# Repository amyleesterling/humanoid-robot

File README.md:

# Project Button — build convergence

**Selected engineering candidate: HR30-TETHER-LIGHT4-P0.1. Not a build release.**

Button remains a complete 762 mm humanoid with 25 active axes, two functional hands, a face, audio/vision, conversational intelligence, and a local deterministic motion boundary. Whole-body walking remains the goal. An instrumented joint is development equipment, not a replacement deliverable. Tether-first testing does not silently remove the eventual onboard-power and untethered requirements.

## Start here

[Active whole-body visual guide](hr30/whole-body-p0.1/active-light4-p0.1/index.html) · [Complete engineering showcase](hr30/whole-body-p0.1/index.html) · [Critical-joint test package](hr30/build-release/critical-joint-test.md) · [Open release decisions](hr30/build-release/blockers.csv)

The machine-readable [baseline lock](hr30/build-release/baseline.lock.json) selects exact existing artifacts at commit `174691255409336a7e25ba1505217859c98c3f80`; it does not regenerate or copy the robot. This is the entry point for the build-release sprint. Older generated package pages retain historical values and must not override these explicit roles.

| Role | Selected source / boundary |
| --- | --- |
| Whole-body geometry | `lightweight-hip-successor-p0.1/HR-30_light4_whole_body_candidate.step` and matching GLB under `hr30/whole-body-p0.1/` |
| Dynamics model | `active-light4-p0.1/hr30_tether_light4_active.urdf` and `.xml` |
| Existing control evidence | `active-light4-p0.1/hr30_tether_light4_ideal_fixture.xml`; the base is supported by a six-degree-of-freedom trajectory weld, not free balance |
| Current planning mass | 9.879813509 kg; 0.120186491 kg below the 10 kg ceiling; no as-built mass or adequate reserve demonstrated |
| Hip pitch/roll | LIGHT4 4:1 on four axes; the old 1.5:1 pitch / 2:1 roll allocation rows are explicitly superseded |
| First test candidate | `R_ANKLE_PITCH`, XM430-W350-R with the LD-25 2.5:1 drive; decision experiment, not approved hardware |
| Other systems | Existing electrical, harness and software packages remain candidates; cross-system build-release reconciliation is open |

The 9.928 kg base ledger and the earlier control-successor result are not the selected LIGHT4 mass/control evidence. The older allocation CSV is reused for its unchanged ankle definition, not adopted wholesale as the active hip allocation. The checker records those four supersessions explicitly.

## Reproduce this sprint's checks

Python 3.10+; standard library only. No network, hardware connection, CAD toolchain, or simulator is invoked.

```sh
python tools/check_hr30_build_baseline.py
python -m unittest discover -s tests -p 'test_hr30_build_baseline.py' -v
# Optional: verify the nine referenced larger assets, if present locally.
python tools/check_hr30_build_baseline.py --full-assets
```

Default execution verifies the exact SHA-256 of three small source files, checks all 23 rotary demand rows and the reduced-leg allocation, reproduces the mass and joint-selection arithmetic, and totals the budget. The two grippers are not silently counted as rotary torque rows. `--full-assets` hashes additional files; even that does not validate geometry, structural capacity, or physics.

On 2026-09-25, the default audit ran against three connector-retrieved source snapshots whose bytes matched the existing source-manifest hashes. **31 synthetic software tests passed**, including stale hashes, missing/duplicate axes, NaN, invalid ratios, authority promotion, wrong adapters, and budget errors. See [the generated audit result](hr30/build-release/validation.json). No complete clone, large-asset audit, CAD rebuild, simulation rerun, physical test or independent engineering approval occurred in this sprint.

## The decision-driving finding

The pinned ideal-fixture table gives right ankle pitch 6.433 Nm peak and 5.645 Nm RMS, about 85% of its linear current-limited endpoint. The [manufacturer](https://robotis.us/products/dynamixel-xm430-w350-r) lists 0.82 Nm as an **estimated** continuous motor torque, explicitly calculated as 20% of stall torque. At the model's 2.5:1 reduction and assumed 85% efficiency, that heuristic becomes 1.7425 Nm at the joint. The modeled RMS demand is approximately 3.24 times that value.

This is a significant sizing question, not a proven thermal failure or a test acceptance limit. Fixture-assisted demand, joint RMS torque, motor current and real thermal duty are not interchangeable. The next physical decision is whether to retain or revise this actuator/transmission combination after independent load-profile review and measurement. No full-leg or whole-robot bulk order is justified by the present endpoint pass.

## First-tranche planning cost

The [budget](hr30/build-release/first-tranche-budget.json) records $392.16 in displayed catalog prices for one actuator, U2D2 and hub. Including explicitly unquoted allowances for review, a guarded joint fixture, drivetrain parts, laboratory access, execution, protection and one rebuild gives **roughly $3,500–$8,600 before tax/shipping**. This is a scope-planning range, not a supplier quote or spending request. Availability and exact product revisions are unconfirmed; existing owned equipment has not been verified.

## Work boundaries and next gate

The test package states the required inputs and decisions for a qualified mechanical/electrical integration partner. It is review-ready as a brief, **not ready to fabricate or energize**. A priced supplier scope, reviewed load waveform, fixture/protection design, numeric abort/acceptance limits and Amy's explicit spending/fabrication approval are still required.

Do not change firmware to permit motion, remove physical holds, order parts, rewrite Git history, or revive the archived arm-only analysis chain in response to this source audit passing. Children remain outside preliminary powered test areas; any later child-adjacent use is a separately reviewed end state.

The [previous full README](README.pre-build-release-2026-09-25.md) is preserved byte-for-byte using its existing Git blob. Its relative links retain their original repository-root context. All historical models, traces, rejection evidence and guides remain in place. This sprint adds no generated STEP/GLB or duplicate release bundle.

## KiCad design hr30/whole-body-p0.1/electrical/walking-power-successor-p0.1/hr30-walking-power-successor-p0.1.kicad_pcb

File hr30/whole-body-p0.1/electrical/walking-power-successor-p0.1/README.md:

# HR-30 walking-power successor P0.1

**PRELIMINARY - WALKING-POWER ARCHITECTURE CANDIDATE ONLY - NOT APPROVED FOR PROCUREMENT, FABRICATION, CONNECTION, POWERED TESTING, MOTION OR ENERGIZATION**

This package provides the native KiCad and web artifacts for a paired TPS259482L bidirectional actuator-branch candidate. One eFuse protects each current direction across every populated axis. The corrected topology uses eight electrically separate one-bus board instances and explicitly rejects the earlier five-board grouping that would have cross-connected independent feeds. The package now contains the exact TI YWP0012A example land pattern and a routed 150 x 68 mm ten-layer board candidate with ERC 0/0, DRC 0/0 and zero unconnected pads. Eight downstream contactor-open brake/dump circuits, exact settings, production stackup, DFM, thermal evidence and all powered-work authority remain open.

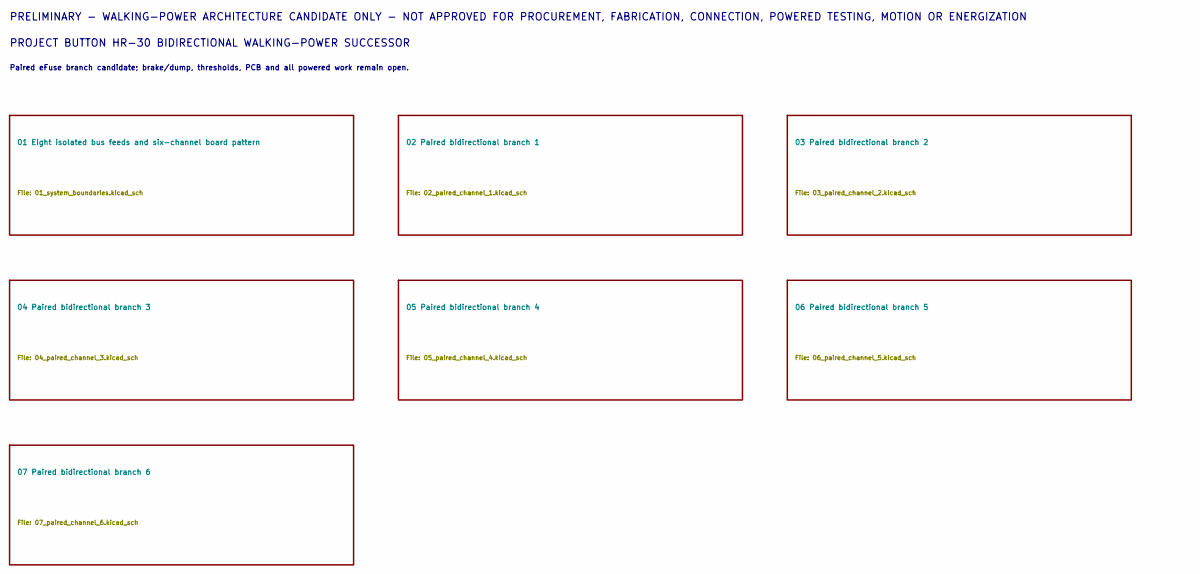
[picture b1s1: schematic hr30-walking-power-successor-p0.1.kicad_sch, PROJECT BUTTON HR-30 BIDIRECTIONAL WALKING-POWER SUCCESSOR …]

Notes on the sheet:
PRELIMINARY - WALKING-POWER ARCHITECTURE CANDIDATE ONLY - NOT APPROVED FOR PROCUREMENT, FABRICATION, CONNECTION, POWERED TESTING, MOTION OR ENERGIZATION
PROJECT BUTTON HR-30 BIDIRECTIONAL WALKING-POWER SUCCESSOR
Paired eFuse branch candidate; brake/dump, thresholds, PCB and all powered work remain open.

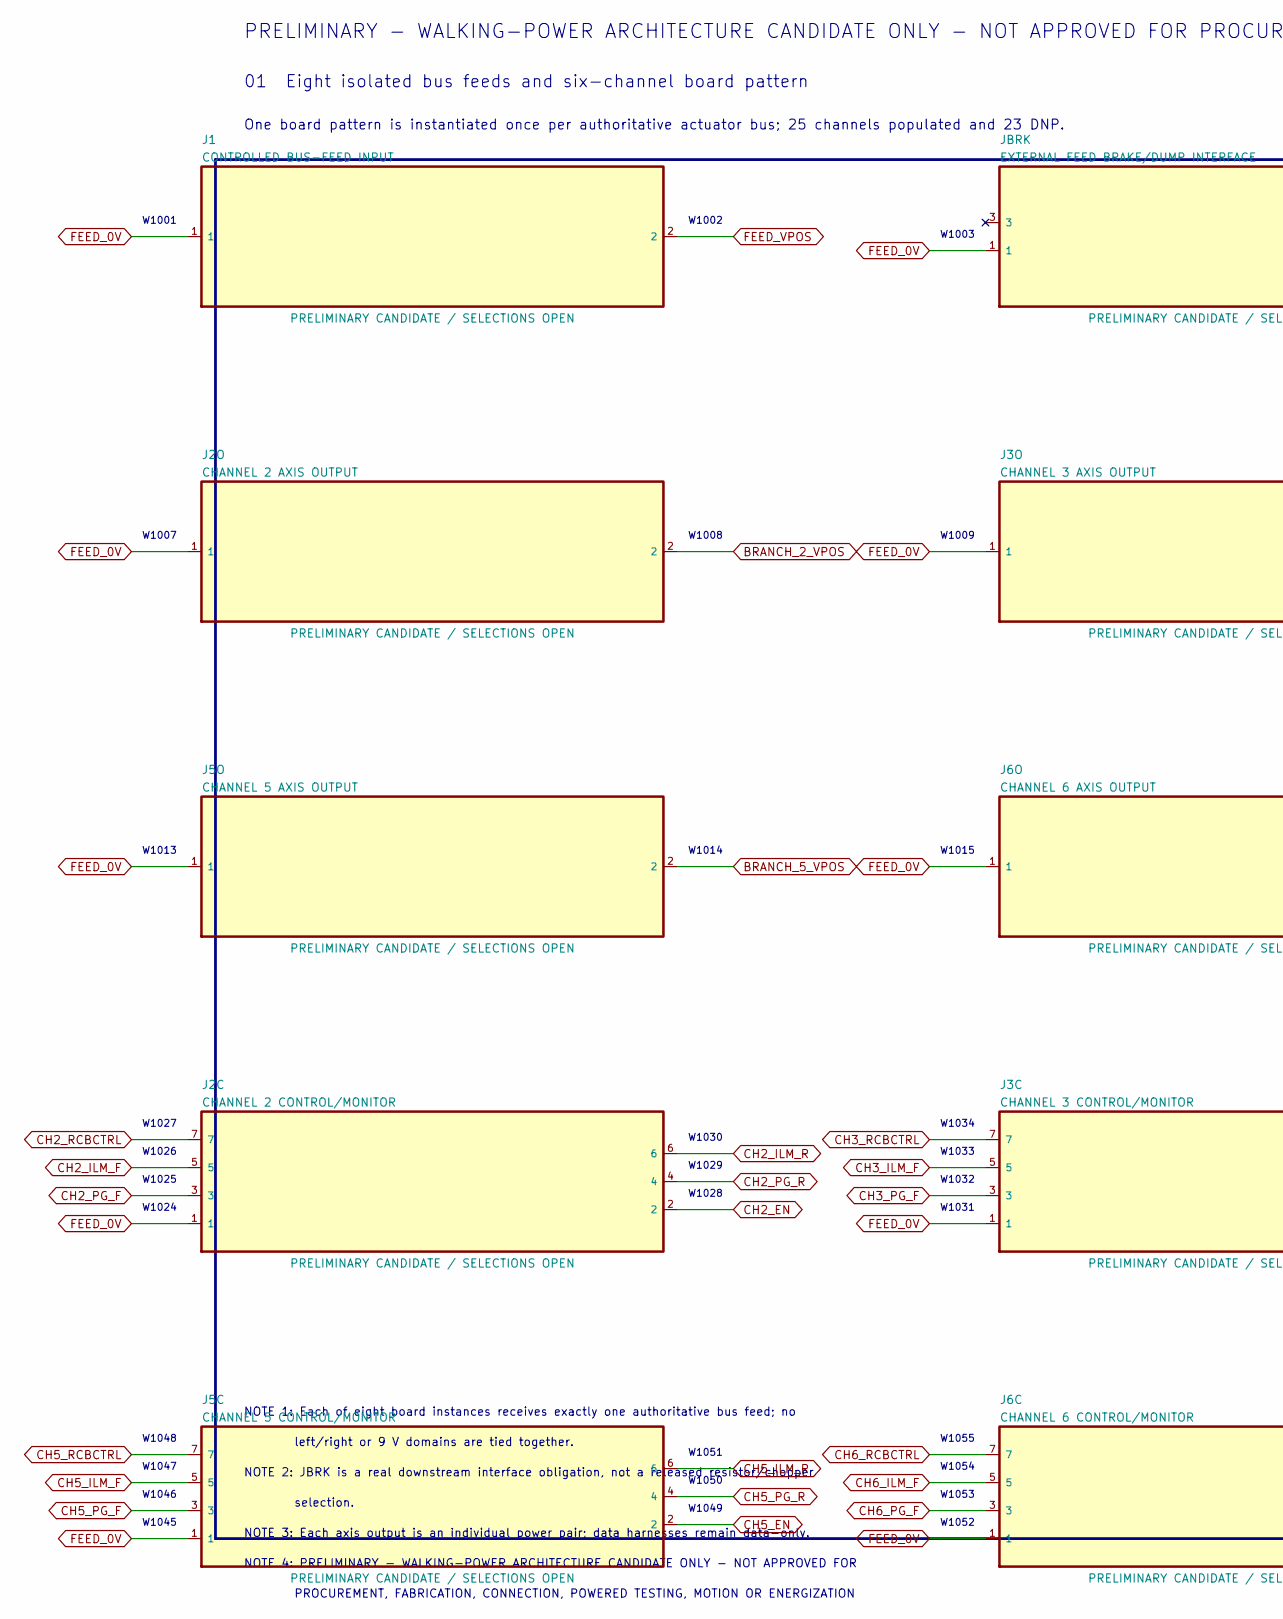
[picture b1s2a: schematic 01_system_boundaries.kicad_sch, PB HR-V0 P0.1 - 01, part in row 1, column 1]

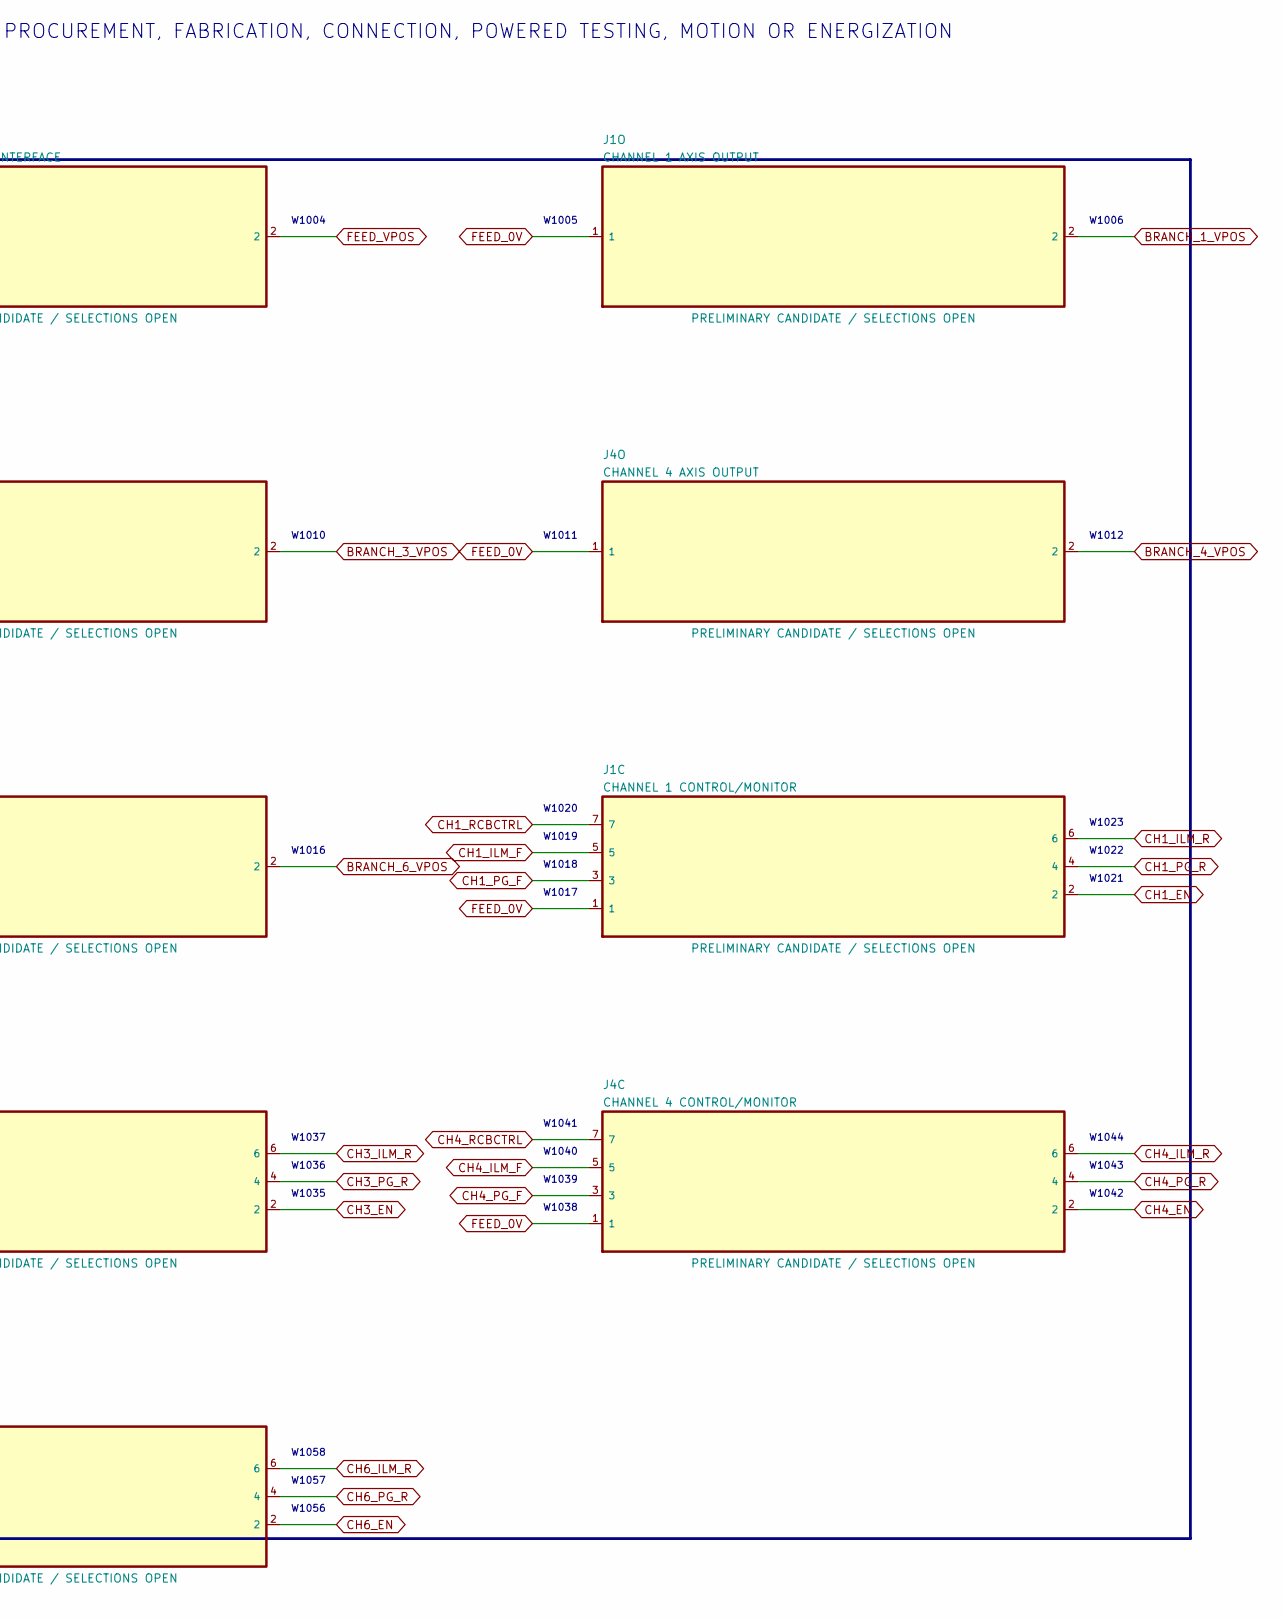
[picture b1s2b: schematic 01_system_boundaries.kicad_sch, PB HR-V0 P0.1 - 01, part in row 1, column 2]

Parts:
J1: CONTROLLED BUS-FEED INPUT; TerminalBlock_MetzConnect_Type703_RT10N02HGLU_1x02_P9.52mm_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
J1C: CHANNEL 1 CONTROL/MONITOR; JST_GH_BM07B-GHS-TBT_1x07-1MP_P1.25mm_Vertical
J1O: CHANNEL 1 AXIS OUTPUT; JST_VH_B2P-VH_1x02_P3.96mm_Vertical
J2C: CHANNEL 2 CONTROL/MONITOR; JST_GH_BM07B-GHS-TBT_1x07-1MP_P1.25mm_Vertical
J2O: CHANNEL 2 AXIS OUTPUT; JST_VH_B2P-VH_1x02_P3.96mm_Vertical
J3C: CHANNEL 3 CONTROL/MONITOR; JST_GH_BM07B-GHS-TBT_1x07-1MP_P1.25mm_Vertical
J3O: CHANNEL 3 AXIS OUTPUT; JST_VH_B2P-VH_1x02_P3.96mm_Vertical
J4C: CHANNEL 4 CONTROL/MONITOR; JST_GH_BM07B-GHS-TBT_1x07-1MP_P1.25mm_Vertical
J4O: CHANNEL 4 AXIS OUTPUT; JST_VH_B2P-VH_1x02_P3.96mm_Vertical
J5C: CHANNEL 5 CONTROL/MONITOR; JST_GH_BM07B-GHS-TBT_1x07-1MP_P1.25mm_Vertical
J5O: CHANNEL 5 AXIS OUTPUT; JST_VH_B2P-VH_1x02_P3.96mm_Vertical
J6C: CHANNEL 6 CONTROL/MONITOR; JST_GH_BM07B-GHS-TBT_1x07-1MP_P1.25mm_Vertical
J6O: CHANNEL 6 AXIS OUTPUT; JST_VH_B2P-VH_1x02_P3.96mm_Vertical
JBRK: EXTERNAL FEED BRAKE/DUMP INTERFACE; JST_VH_B3P-VH_1x03_P3.96mm_Vertical

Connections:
BRANCH_1_VPOS: J1O.2; also elsewhere on the board
BRANCH_2_VPOS: J2O.2; also elsewhere on the board
BRANCH_3_VPOS: J3O.2; also elsewhere on the board
BRANCH_4_VPOS: J4O.2; also elsewhere on the board
BRANCH_5_VPOS: J5O.2; also elsewhere on the board
BRANCH_6_VPOS: J6O.2; also elsewhere on the board
CH1_EN: J1C.2; also elsewhere on the board
CH1_ILM_F: J1C.5; also elsewhere on the board
CH1_ILM_R: J1C.6; also elsewhere on the board
CH1_PG_F: J1C.3; also elsewhere on the board
CH1_PG_R: J1C.4; also elsewhere on the board
CH1_RCBCTRL: J1C.7; also elsewhere on the board
CH2_EN: J2C.2; also elsewhere on the board
CH2_ILM_F: J2C.5; also elsewhere on the board
CH2_ILM_R: J2C.6; also elsewhere on the board
CH2_PG_F: J2C.3; also elsewhere on the board
CH2_PG_R: J2C.4; also elsewhere on the board
CH2_RCBCTRL: J2C.7; also elsewhere on the board
CH3_EN: J3C.2; also elsewhere on the board
CH3_ILM_F: J3C.5; also elsewhere on the board
CH3_ILM_R: J3C.6; also elsewhere on the board
CH3_PG_F: J3C.3; also elsewhere on the board
CH3_PG_R: J3C.4; also elsewhere on the board
CH3_RCBCTRL: J3C.7; also elsewhere on the board
CH4_EN: J4C.2; also elsewhere on the board
CH4_ILM_F: J4C.5; also elsewhere on the board
CH4_ILM_R: J4C.6; also elsewhere on the board
CH4_PG_F: J4C.3; also elsewhere on the board
CH4_PG_R: J4C.4; also elsewhere on the board
CH4_RCBCTRL: J4C.7; also elsewhere on the board
CH5_EN: J5C.2; also elsewhere on the board
CH5_ILM_F: J5C.5; also elsewhere on the board
CH5_ILM_R: J5C.6; also elsewhere on the board
CH5_PG_F: J5C.3; also elsewhere on the board
CH5_PG_R: J5C.4; also elsewhere on the board
CH5_RCBCTRL: J5C.7; also elsewhere on the board
CH6_EN: J6C.2; also elsewhere on the board
CH6_ILM_F: J6C.5; also elsewhere on the board
CH6_ILM_R: J6C.6; also elsewhere on the board
CH6_PG_F: J6C.3; also elsewhere on the board
CH6_PG_R: J6C.4; also elsewhere on the board
CH6_RCBCTRL: J6C.7; also elsewhere on the board
DUMP_DIAG: JBRK.3
FEED_0V: J1.1, J1C.1, J1O.1, J2C.1, J2O.1, J3C.1, J3O.1, J4C.1, J4O.1, J5C.1, J5O.1, J6C.1, J6O.1, JBRK.1; also elsewhere on the board
FEED_VPOS: J1.2, JBRK.2; also elsewhere on the board

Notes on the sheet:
PRELIMINARY - WALKING-POWER ARCHITECTURE CANDIDATE ONLY - NOT APPROVED FOR PROCUREMENT, FABRICATION, CONNECTION, POWERED TESTING, MOTION OR ENERGIZATION
01 Eight isolated bus feeds and six-channel board pattern
One board pattern is instantiated once per authoritative actuator bus; 25 channels populated and 23 DNP.
W1001
W1002
W1003
W1004
W1005
W1006
W1007
W1008
W1009
W1010
W1011
W1012
W1013
W1014
W1015
W1016
W1017
W1018
W1019
W1020
W1021
W1022
W1023
W1024
W1025
W1026
W1027
W1028
W1029
W1030
W1031
W1032
W1033
W1034
W1035
W1036
W1037

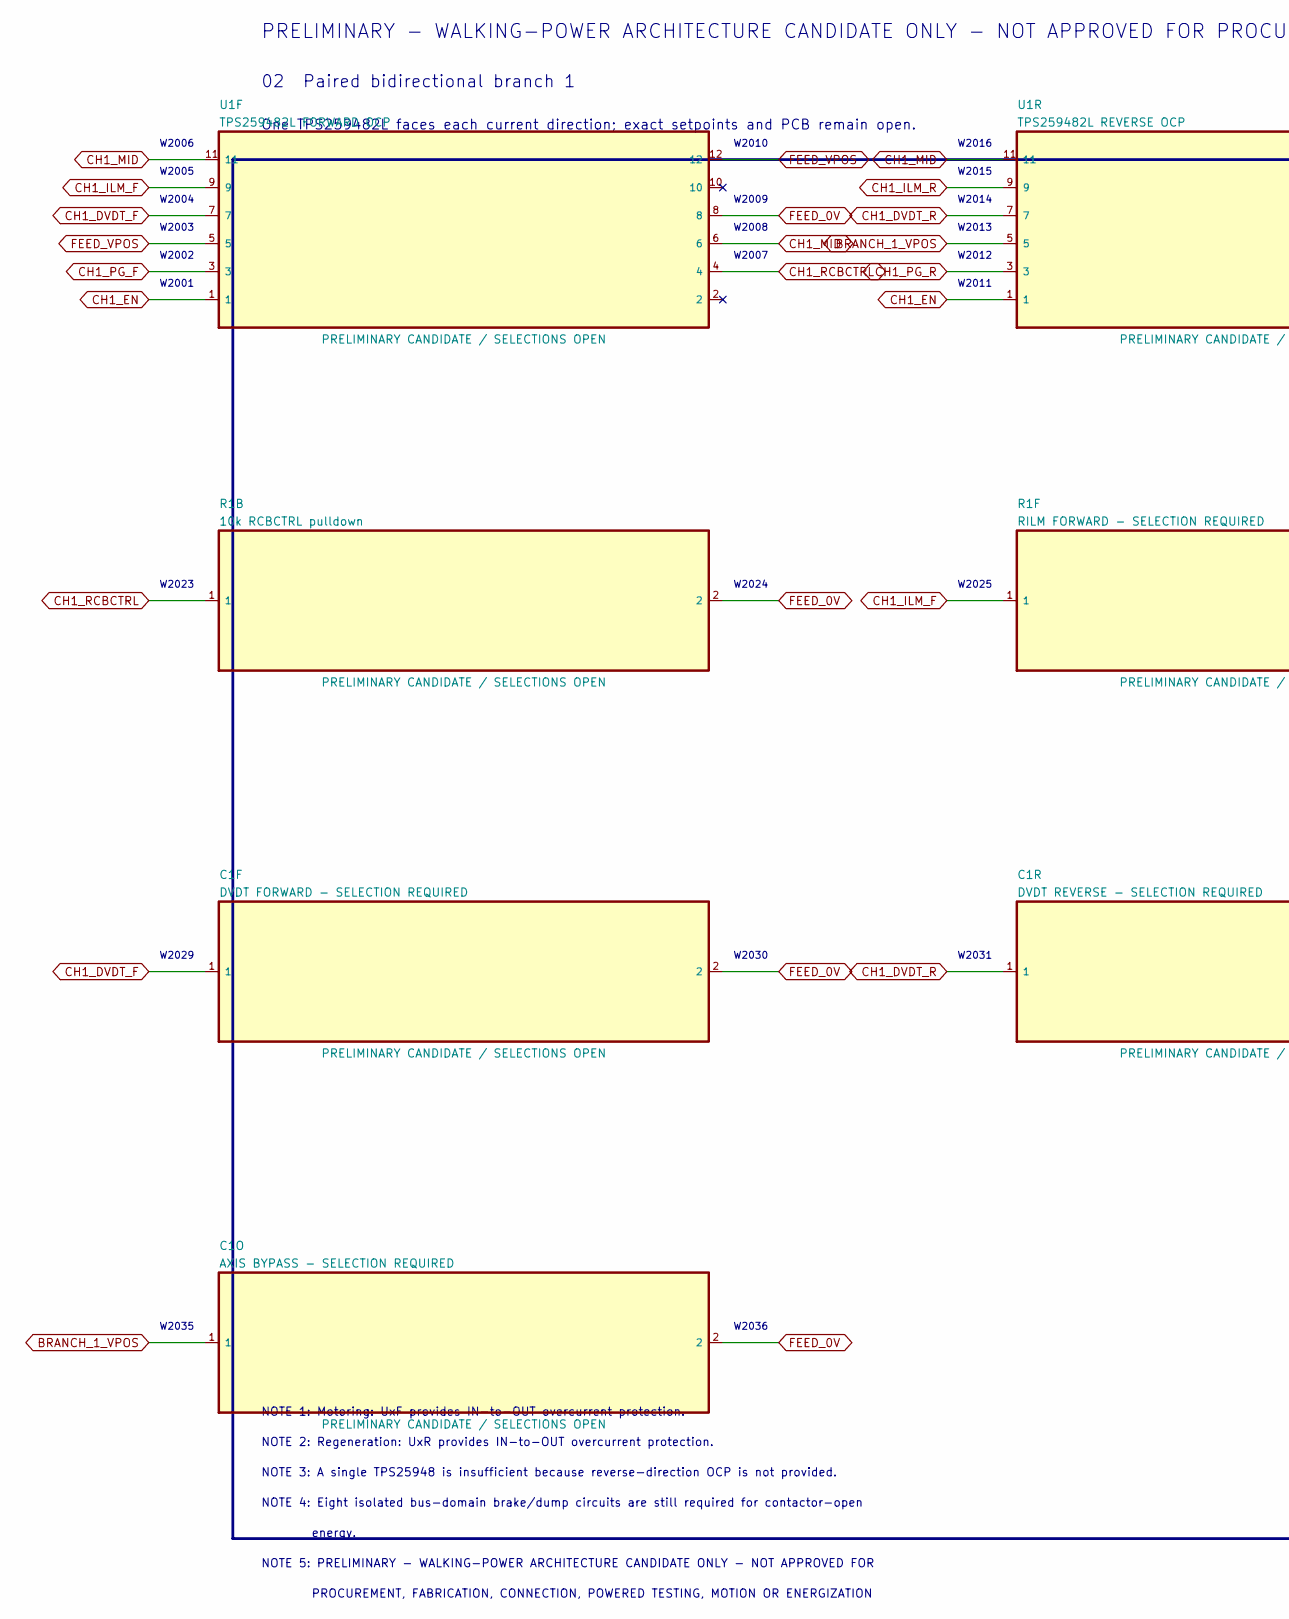
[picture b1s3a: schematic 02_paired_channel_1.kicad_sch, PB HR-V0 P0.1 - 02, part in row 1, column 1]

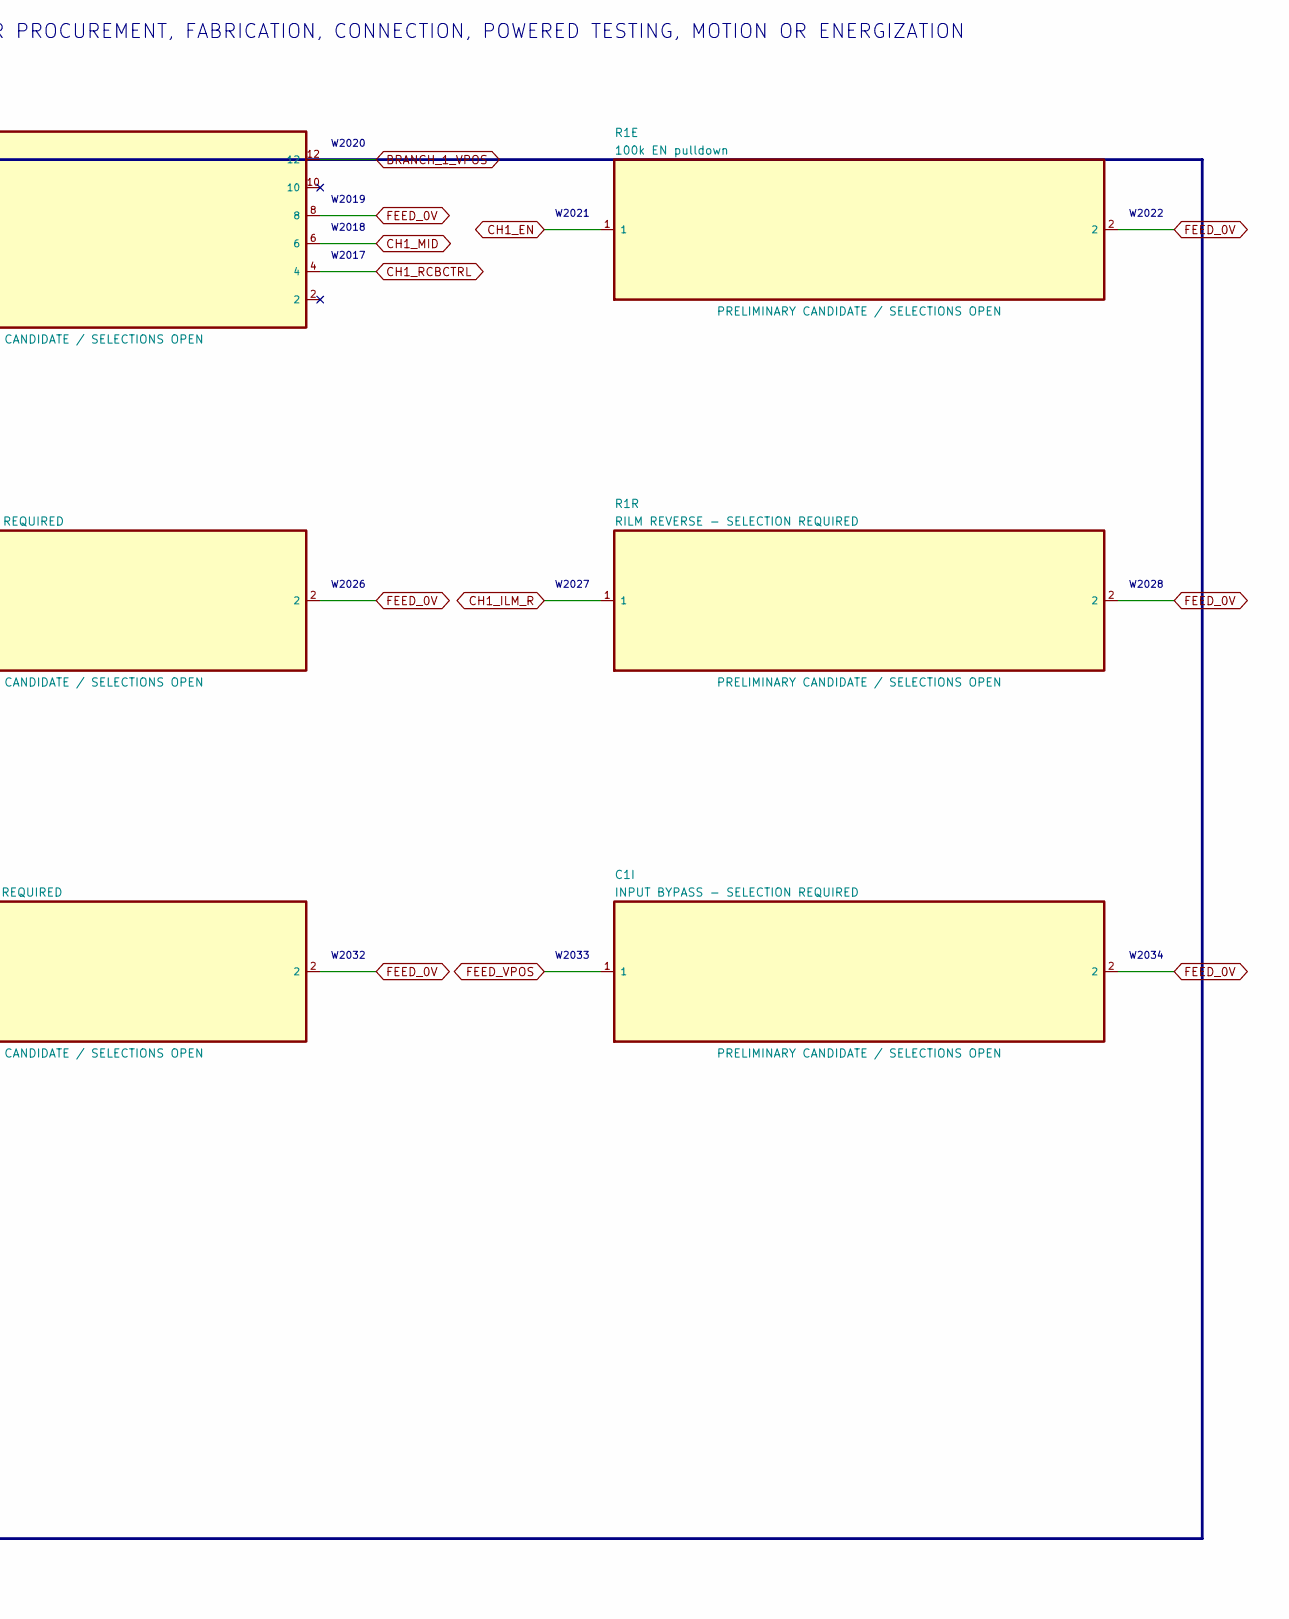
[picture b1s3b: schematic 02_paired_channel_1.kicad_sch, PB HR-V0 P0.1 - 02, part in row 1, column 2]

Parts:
C1F: DVDT FORWARD - SELECTION REQUIRED; C_0603_1608Metric
C1I: INPUT BYPASS - SELECTION REQUIRED; C_0805_2012Metric
C1O: AXIS BYPASS - SELECTION REQUIRED; C_0805_2012Metric
C1R: DVDT REVERSE - SELECTION REQUIRED; C_0603_1608Metric
R1B: 10k RCBCTRL pulldown; R_0603_1608Metric
R1E: 100k EN pulldown; R_0603_1608Metric
R1F: RILM FORWARD - SELECTION REQUIRED; R_0603_1608Metric
R1R: RILM REVERSE - SELECTION REQUIRED; R_0603_1608Metric
U1F: TPS259482L FORWARD OCP
U1R: TPS259482L REVERSE OCP

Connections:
BRANCH_1_VPOS: C1O.1, U1R.5, U1R.12; also elsewhere on the board
CH1_DVDT_F: C1F.1, U1F.7
CH1_DVDT_R: C1R.1, U1R.7
CH1_EN: R1E.1, U1F.1, U1R.1; also elsewhere on the board
CH1_ILM_F: R1F.1, U1F.9; also elsewhere on the board
CH1_ILM_R: R1R.1, U1R.9; also elsewhere on the board
CH1_ITIMER_F: U1F.10
CH1_ITIMER_R: U1R.10
CH1_MID: U1F.6, U1F.11, U1R.6, U1R.11
CH1_OV_F: U1F.2; also elsewhere on the board
CH1_OV_R: U1R.2; also elsewhere on the board
CH1_PG_F: U1F.3; also elsewhere on the board
CH1_PG_R: U1R.3; also elsewhere on the board
CH1_RCBCTRL: R1B.1, U1F.4, U1R.4; also elsewhere on the board
FEED_0V: C1F.2, C1I.2, C1O.2, C1R.2, R1B.2, R1E.2, R1F.2, R1R.2, U1F.8, U1R.8; also elsewhere on the board
FEED_VPOS: C1I.1, U1F.5, U1F.12; also elsewhere on the board

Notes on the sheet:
PRELIMINARY - WALKING-POWER ARCHITECTURE CANDIDATE ONLY - NOT APPROVED FOR PROCUREMENT, FABRICATION, CONNECTION, POWERED TESTING, MOTION OR ENERGIZATION
02 Paired bidirectional branch 1
One TPS259482L faces each current direction; exact setpoints and PCB remain open.
W2001
W2002
W2003
W2004
W2005
W2006
W2007
W2008
W2009
W2010
W2011
W2012
W2013
W2014
W2015
W2016
W2017
W2018
W2019
W2020
W2021
W2022
W2023
W2024
W2025
W2026
W2027
W2028
W2029
W2030
W2031
W2032
W2033
W2034
W2035
W2036
NOTE 1: Motoring: UxF provides IN-to-OUT overcurrent protection.

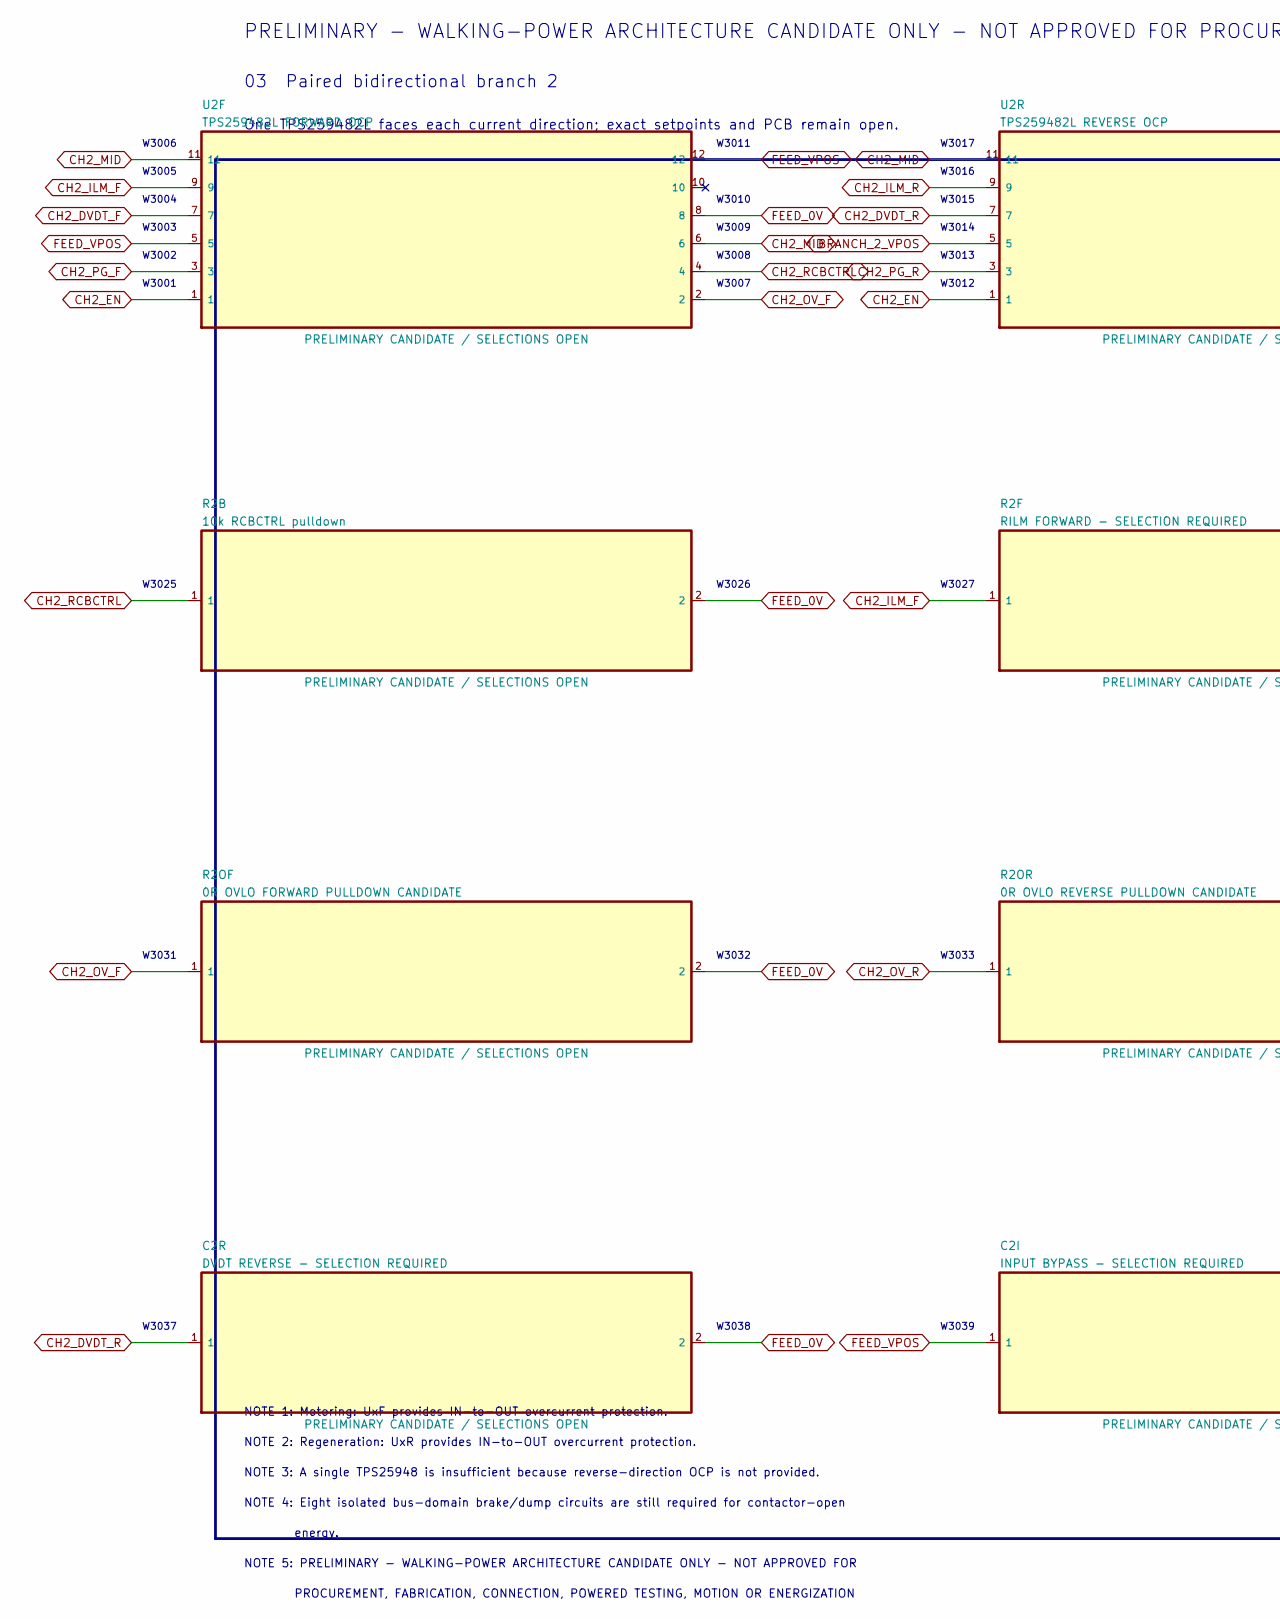
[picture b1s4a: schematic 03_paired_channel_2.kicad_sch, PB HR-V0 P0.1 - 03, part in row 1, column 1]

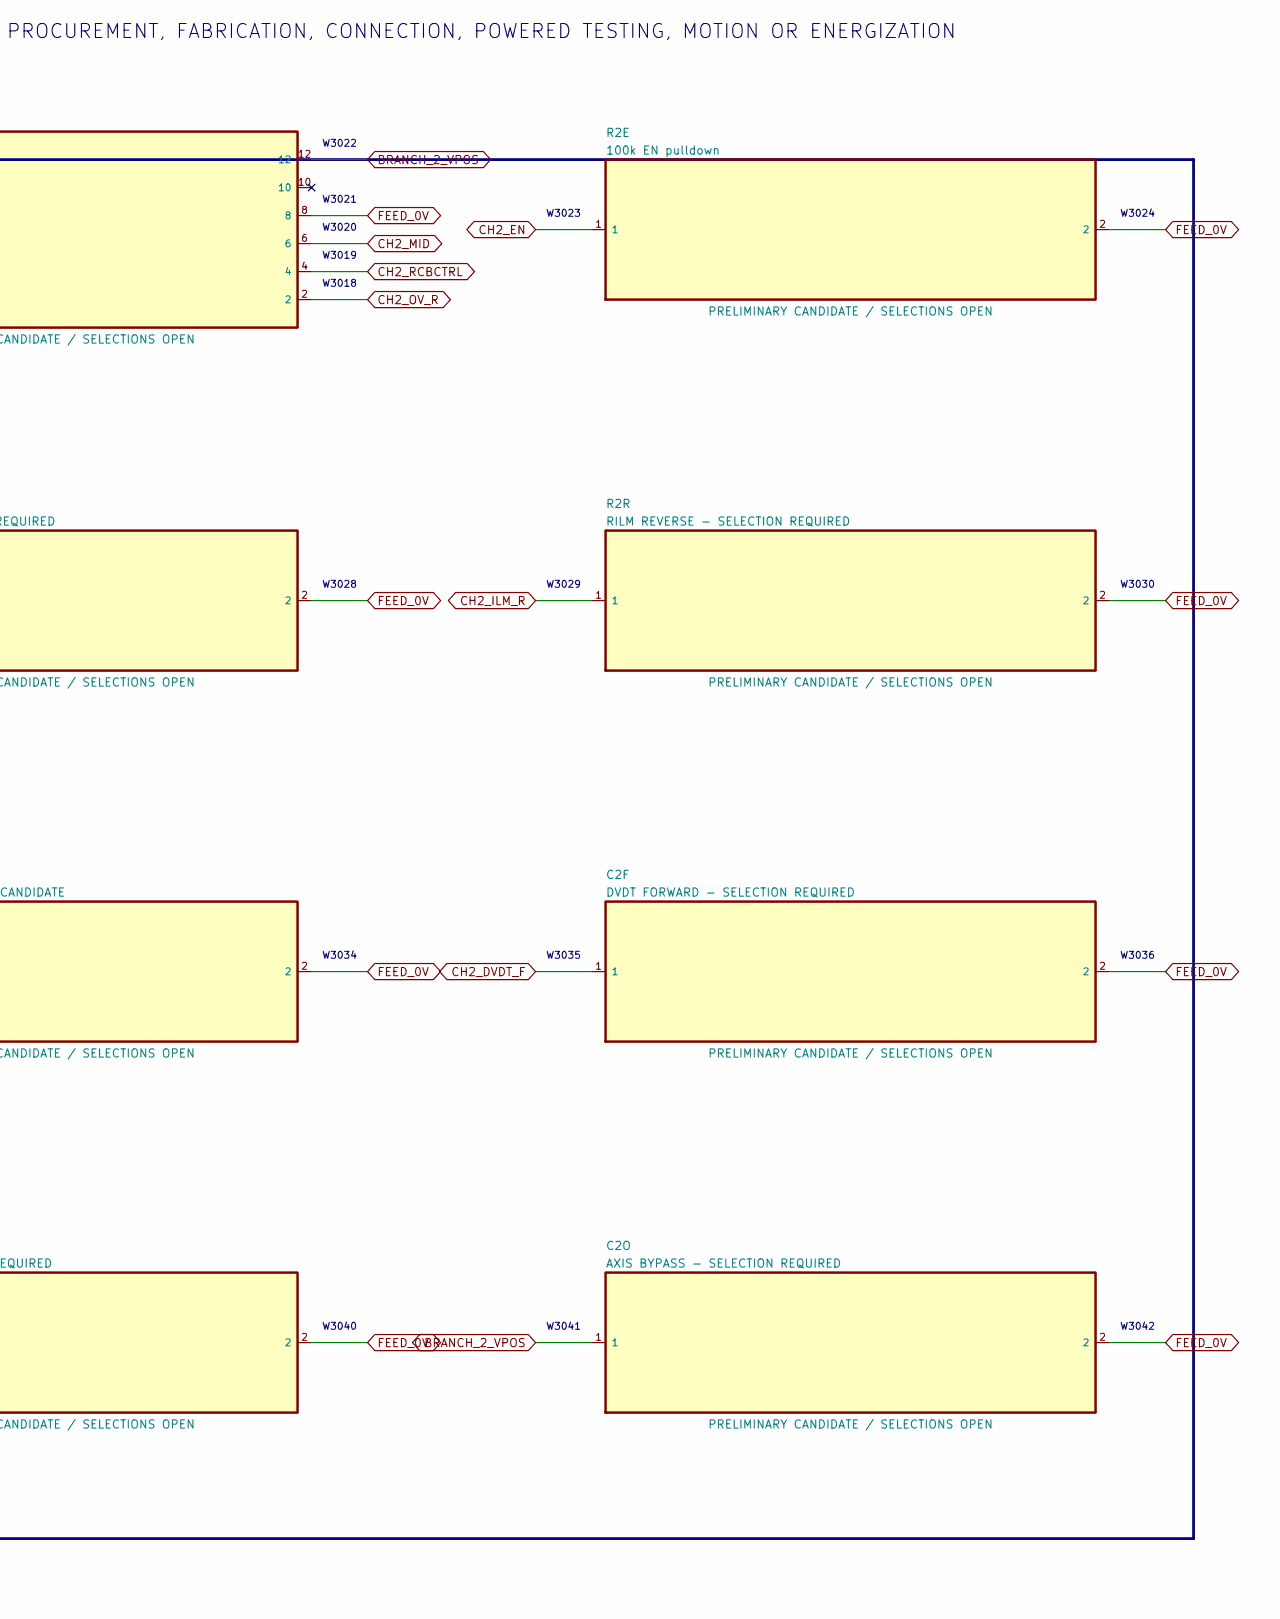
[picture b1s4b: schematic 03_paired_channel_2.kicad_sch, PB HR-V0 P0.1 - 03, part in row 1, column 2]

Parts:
C2F: DVDT FORWARD - SELECTION REQUIRED; C_0603_1608Metric
C2I: INPUT BYPASS - SELECTION REQUIRED; C_0805_2012Metric
C2O: AXIS BYPASS - SELECTION REQUIRED; C_0805_2012Metric
C2R: DVDT REVERSE - SELECTION REQUIRED; C_0603_1608Metric
R2B: 10k RCBCTRL pulldown; R_0603_1608Metric
R2E: 100k EN pulldown; R_0603_1608Metric
R2F: RILM FORWARD - SELECTION REQUIRED; R_0603_1608Metric
R2OF: 0R OVLO FORWARD PULLDOWN CANDIDATE; R_0603_1608Metric
R2OR: 0R OVLO REVERSE PULLDOWN CANDIDATE; R_0603_1608Metric
R2R: RILM REVERSE - SELECTION REQUIRED; R_0603_1608Metric
U2F: TPS259482L FORWARD OCP; TI_YWP0012A_PowerWCSP_2.441x1.728mm
U2R: TPS259482L REVERSE OCP; TI_YWP0012A_PowerWCSP_2.441x1.728mm

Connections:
BRANCH_2_VPOS: C2O.1, U2R.5, U2R.12; also elsewhere on the board
CH2_DVDT_F: C2F.1, U2F.7
CH2_DVDT_R: C2R.1, U2R.7
CH2_EN: R2E.1, U2F.1, U2R.1; also elsewhere on the board
CH2_ILM_F: R2F.1, U2F.9; also elsewhere on the board
CH2_ILM_R: R2R.1, U2R.9; also elsewhere on the board
CH2_ITIMER_F: U2F.10
CH2_ITIMER_R: U2R.10
CH2_MID: U2F.6, U2F.11, U2R.6, U2R.11
CH2_OV_F: R2OF.1, U2F.2
CH2_OV_R: R2OR.1, U2R.2
CH2_PG_F: U2F.3; also elsewhere on the board
CH2_PG_R: U2R.3; also elsewhere on the board
CH2_RCBCTRL: R2B.1, U2F.4, U2R.4; also elsewhere on the board
FEED_0V: C2F.2, C2I.2, C2O.2, C2R.2, R2B.2, R2E.2, R2F.2, R2OF.2, R2OR.2, R2R.2, U2F.8, U2R.8; also elsewhere on the board
FEED_VPOS: C2I.1, U2F.5, U2F.12; also elsewhere on the board

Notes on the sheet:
PRELIMINARY - WALKING-POWER ARCHITECTURE CANDIDATE ONLY - NOT APPROVED FOR PROCUREMENT, FABRICATION, CONNECTION, POWERED TESTING, MOTION OR ENERGIZATION
03 Paired bidirectional branch 2
One TPS259482L faces each current direction; exact setpoints and PCB remain open.
W3001
W3002
W3003
W3004
W3005
W3006
W3007
W3008
W3009
W3010
W3011
W3012
W3013
W3014
W3015
W3016
W3017
W3018
W3019
W3020
W3021
W3022
W3023
W3024
W3025
W3026
W3027
W3028
W3029
W3030
W3031
W3032
W3033
W3034
W3035
W3036
W3037
